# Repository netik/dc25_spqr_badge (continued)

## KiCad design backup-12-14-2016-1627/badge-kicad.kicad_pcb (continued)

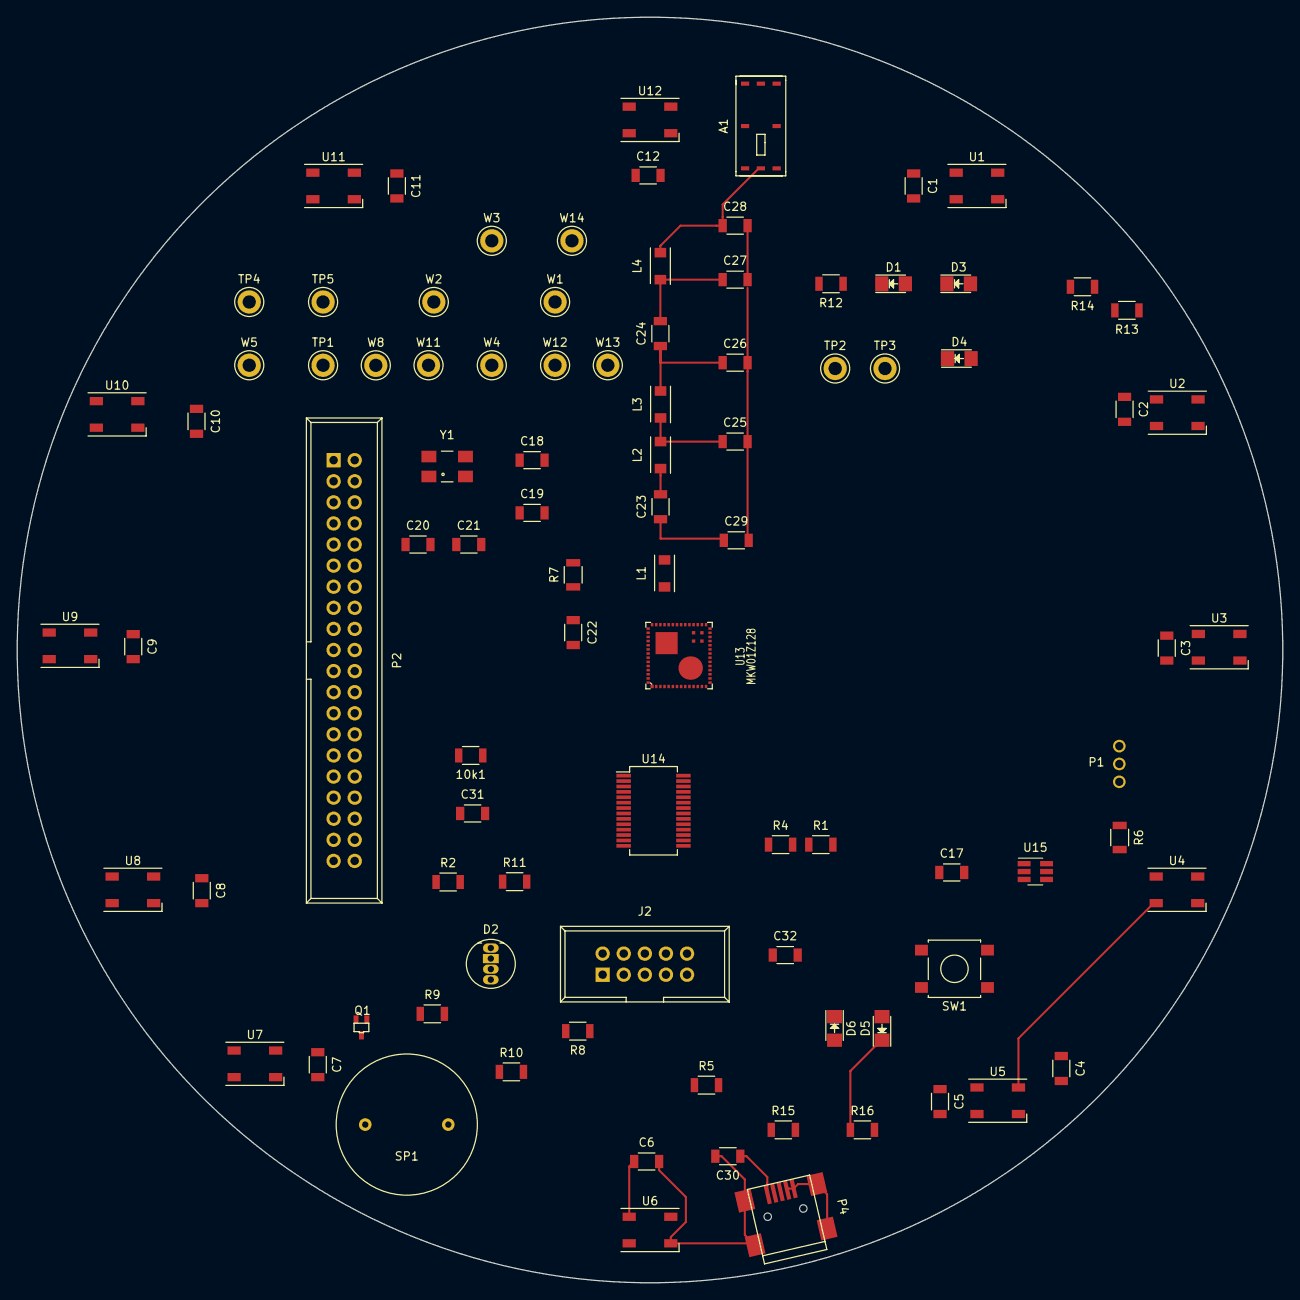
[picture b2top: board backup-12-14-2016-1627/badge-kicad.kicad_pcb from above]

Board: 4 copper layers, 152.4 x 152.4 mm, 94 parts (1 on the bottom side), 72 nets.

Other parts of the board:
10k1: R; R_1206

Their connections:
unnamed 11: 10k1.1; also elsewhere on the board
VUSB: 10k1.2; also elsewhere on the board

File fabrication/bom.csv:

reference_designator,qty,mpn,value,description,partcost,laborcost
A1,1,7488910092,7488910092_ANTENNA,SMD Aerial [Würth Elektronik] 7488910092 SMD Aerial,4.884,0.555
BT1,1,1769,Battery 3.7v 1000mAh,JST-PH 2-Pin SMT Right Angle Connector,0.990,0.270
C1,1,MF-CAP-0805-0.1uF,100nF,Capacitor MLCC 0805 0.1uF -20% +80% 50V,0.169,0.000
C10,1,MF-CAP-0805-0.1uF,100nF,Capacitor MLCC 0805 0.1uF -20% +80% 50V,0.169,0.000
C11,1,MF-CAP-0805-0.1uF,100nF,Capacitor MLCC 0805 0.1uF -20% +80% 50V,0.169,0.000
C12,1,MF-CAP-0805-0.1uF,100nF,Capacitor MLCC 0805 0.1uF -20% +80% 50V,0.169,0.000
C13,1,MF-CAP-0805-1uF,1uF,"Capacitor MLCC 0805 1uF -20%, +80% 16V",0.066,0.000
C14,1,CL21A106KQFNNNG,10uF,CL21 Series 10 uF 6.3V ±10 % Tolerance X5R SMT Multilayer Ceramic Capacitor,0.396,1.665
C15,1,CL21A106KQFNNNG,10uF,CL21 Series 10 uF 6.3V ±10 % Tolerance X5R SMT Multilayer Ceramic Capacitor,0.396,1.665
C17,1,GRM21BR60G107ME15L,100uF,0805 100 uF 4 V ±20% Tolerance X5R Multilayer Ceramic Chip Capacitor,1.558,0.270
C2,1,MF-CAP-0805-0.1uF,100nF,Capacitor MLCC 0805 0.1uF -20% +80% 50V,0.169,0.000
C20,1,MF-CAP-0805-0.1uF,100nF,Capacitor MLCC 0805 0.1uF -20% +80% 50V,0.169,0.000
C21,1,MF-CAP-0805-0.1uF,100nF,Capacitor MLCC 0805 0.1uF -20% +80% 50V,0.169,0.000
C22,1,MF-CAP-0805-0.1uF,0.1uF,Capacitor MLCC 0805 0.1uF -20% +80% 50V,0.165,0.000
C23,1,08051A6R8CAT2A,6.8pF,Capacitor; Ceramic; Cap 6.8 pF; Tol 0.25 pF; Vol-Rtg 100 VDC; SMT; 0805; C0G(NPO); TR,0.224,0.270
C24,1,CC0805JRNPO9BN101,100pF,0805 100 pF 50 V ±5 % Tolerance NPO Surface Mount Ceramic Capacitor,0.132,0.270
C25,1,251R15S7R5CV4E,7.5pF,Cap Cer 7.5pf 250v Np0 0805,0.264,0.270
C26,1,08051A5R6CAT2A,5.6pF,0805 5.6 pF 100 V ±0.25 pF Tol. C0G/NP0 SMT Multilayer Ceramic Capacitor,0.356,0.270
C27,1,CL21C1R2BBANNNC,1.2pF,Cap Ceramic 1.2pF 50V C0G 0.1pF SMD 0805 125°C Cardboard T/R,0.264,0.540
C28,1,CL21C1R2BBANNNC,1.2pF,Cap Ceramic 1.2pF 50V C0G 0.1pF SMD 0805 125°C Cardboard T/R,0.264,0.540
C29,1,C0805C209C5GACTU,2.0pF,Cap Ceramic 2pF 50V C0G 0.25pF SMD 0805 125C Paper T/R,0.436,0.270
C3,1,MF-CAP-0805-0.1uF,100nF,Capacitor MLCC 0805 0.1uF -20% +80% 50V,0.169,0.000
C30,1,MF-CAP-0805-0.1uF,0.1uF,Capacitor MLCC 0805 0.1uF -20% +80% 50V,0.165,0.000
C31,1,CL21A106KQFNNNG,10uF,CL21 Series 10 uF 6.3V ±10 % Tolerance X5R SMT Multilayer Ceramic Capacitor,0.396,1.665
C32,1,MF-CAP-0805-0.1uF,0.1uF,Capacitor MLCC 0805 0.1uF -20% +80% 50V,0.165,0.000
C4,1,MF-CAP-0805-0.1uF,100nF,Capacitor MLCC 0805 0.1uF -20% +80% 50V,0.169,0.000
C5,1,MF-CAP-0805-0.1uF,100nF,Capacitor MLCC 0805 0.1uF -20% +80% 50V,0.169,0.000
C6,1,MF-CAP-0805-0.1uF,100nF,Capacitor MLCC 0805 0.1uF -20% +80% 50V,0.169,0.000
C7,1,MF-CAP-0805-0.1uF,100nF,Capacitor MLCC 0805 0.1uF -20% +80% 50V,0.169,0.000
C8,1,MF-CAP-0805-0.1uF,100nF,Capacitor MLCC 0805 0.1uF -20% +80% 50V,0.169,0.000
C9,1,MF-CAP-0805-0.1uF,100nF,Capacitor MLCC 0805 0.1uF -20% +80% 50V,0.169,0.000
D1,1,MF-LED-0805-RED,RED PWROK,Red LED 638nm 25mcd 0805,0.088,0.000
D2,1,150080BS75000,BLUE SDIO,"LED, 0805, BLUE, 145MCD, 470NM; Bulb Size: -; LED Colour: Bleu; Luminous Intensity",0.238,0.555
D3,1,MF-LED-0805-RED,RED UTX,Red LED 638nm 25mcd 0805,0.088,0.000
D4,1,MF-LED-0805-GREEN,GREEN URX,Green LED 569nm 12mcd 0805,0.088,0.000
D5,1,MF-LED-0805-RED,RED (CHARGING),Red LED 638nm 25mcd 0805,0.088,0.000
D6,1,MF-LED-0805-GREEN,GRN (DONE),Green LED 569nm 12mcd 0805,0.088,0.000
D7,1,MF-LED-0805-RED,RED RFTX,Red LED 638nm 25mcd 0805,0.088,0.000
D8,1,MF-LED-0805-GREEN,GRN RFRX,Green LED 569nm 12mcd 0805,0.088,0.000
J2,1,M50-3500542,JTAG,"Header, Straight, 2row, 10way",1.558,3.330
L1,1,KL732ATTE4N7C,0.0047 uH,Inductor RF Chip Thin Film Multilayer 4.7nH 0.2nH 500MHz 25Q-Factor 700mA 500mOhm DCR 0805 Automotive T/R,0.845,0.270
L2,1,IMC0805ER6N8J01,0.0068 uH,Ind High Frequency Wirewound 6.8nH 5% 250MHz 60Q-Factor Ceramic 600mA 0805 T/R,0.343,0.540
L3,1,IMC0805ER6N8J01,0.0068 uH,Ind High Frequency Wirewound 6.8nH 5% 250MHz 60Q-Factor Ceramic 600mA 0805 T/R,0.343,0.540
L4,1,36502A15NJTDG,15 NH,"Surface Mount High Frequency Inductor, 36502A Series, 15 nH, 5%, 0805 [2012 Metric], 3.4 GHz",0.211,0.270
P1,1,TM1000Q,TM1000,"SENSOR, TILT, 45DEG, 24V; Beam Angle: 45°; Switching Voltage: 24V; Output Current: 20mA; Sensor Body Material: -",2.033,0.555
P2,1,1-215307-0,CONN_02X20,Socket; pin strips; HV-100; female; PIN: 20; straight; 2,3.406,3.330
P4,1,105017-0001,USB_OTG,Conn USB Type B RCP 5 POS 0.65mm Solder RA Thru-Hole 5 Terminal 1 Port Embossed T/R,0.964,0.675
PARTS$0.000,1,,FTDI BACKUP,MPN to consign or search,0.000,0.000
Q1,1,MMBT3904LT1G,MNBT3904,MMBT Series 40 V 200 mA SMT NPN Silicon General Purpose Transistor - SOT-23,0.132,0.405
R1,1,MF-RES-0805-1K,1K,Resistor Thick Film 0805 1K Ohm 5% 125mW 150V,0.055,0.000
R10,1,MF-RES-0805-220,220,Resistor Thick Film 0805 220 Ohm 5% 125mW 150V,0.220,0.000
R11,1,MF-RES-0805-220,220,Resistor Thick Film 0805 220 Ohm 5% 125mW 150V,0.220,0.000
R12,1,MF-RES-0805-220,220,Resistor Thick Film 0805 220 Ohm 5% 125mW 150V,0.220,0.000
R13,1,MF-RES-0805-1K,1k,Resistor Thick Film 0805 1K Ohm 5% 125mW 150V,0.220,0.000
R14,1,MF-RES-0805-1K,1k,Resistor Thick Film 0805 1K Ohm 5% 125mW 150V,0.220,0.000
R15,1,MF-RES-0805-1K,1k,Resistor Thick Film 0805 1K Ohm 5% 125mW 150V,0.220,0.000
R16,1,MF-RES-0805-1K,1k,Resistor Thick Film 0805 1K Ohm 5% 125mW 150V,0.220,0.000
R2,1,MF-RES-0805-100,100,Resistor Thick Film 0805 100 Ohm 5% 125mW 150V,0.110,0.000
R3,1,MF-RES-0805-10K,10k,Resistor Thick Film 0805 10K Ohm 5% 125mW 150V,0.110,0.000
R4,1,MF-RES-0805-100,120,Resistor Thick Film 0805 100 Ohm 5% 125mW 150V,0.055,0.000
R5,1,MF-RES-0805-2K,2k,Resistor Thick Film 0805 2K Ohm5% 125W 150V,0.055,0.000
R6,1,MF-RES-0805-10K,10k,Resistor Thick Film 0805 10K Ohm 5% 125mW 150V,0.110,0.000
R7,1,MF-RES-0805-100,100,Resistor Thick Film 0805 100 Ohm 5% 125mW 150V,0.110,0.000
R8,1,MF-RES-0805-10K,10K,Resistor Thick Film 0805 10K Ohm 5% 125mW 150V,0.055,0.000
R9,1,MF-RES-0805-220,220,Resistor Thick Film 0805 220 Ohm 5% 125mW 150V,0.220,0.000
SP1,1,PS1720P02,TDK PS1720P02,PS Series Ø17 mm 8 x 10 mm 70 dB 3 V 2 KHz Piezoelectronic Buzzer,0.964,0.555
SW1,1,TL3301NF160QG,SW_PUSH,TL3301 Series SPST 1.6 N Round Button Gull Wing Surface Mount Tactile Switch,0.515,0.555
U1,1,WS2812B,WS2812B,Integrated Control Driver RGB LED 5050,2.640,5.178
U10,1,WS2812B,WS2812B,Integrated Control Driver RGB LED 5050,2.640,5.178
U11,1,WS2812B,WS2812B,Integrated Control Driver RGB LED 5050,2.640,5.178
U12,1,WS2812B,WS2812B,Integrated Control Driver RGB LED 5050,2.640,5.178
U13,1,MKW01Z128CHN,MKW01Z128,"Kinetis KW01: sub 1GHz Wireless Radio MCU, 48MHz Cortex-M0+, 128KB Flash, 16KB SRAM, 60-LGA",5.306,3.330
U14,1,FT232RL-TUBE,FT232RL SSOP,USB-to-UART 1-CH 256byte FIFO 5V 28-Pin SSOP Tube,5.940,3.330
U15,1,TPS76333DBVR,TPS76333,"Low Iq, 150-mA, Low-Dropout Linear Regulators 5-SOT-23 -40 to 125",1.175,0.675
U16,1,MCP73831T-2ACI/OT,MCP73831T-2ACI/OT,"supervisor, pin, supply, battery, number, single, voltage, ic, Power Management, current, management, temperature, mi...",0.766,0.675
U2,1,WS2812B,WS2812B,Integrated Control Driver RGB LED 5050,2.640,5.178
U3,1,WS2812B,WS2812B,Integrated Control Driver RGB LED 5050,2.640,5.178
U4,1,WS2812B,WS2812B,Integrated Control Driver RGB LED 5050,2.640,5.178
U5,1,WS2812B,WS2812B,Integrated Control Driver RGB LED 5050,2.640,5.178
U6,1,WS2812B,WS2812B,Integrated Control Driver RGB LED 5050,2.640,5.178
U7,1,WS2812B,WS2812B,Integrated Control Driver RGB LED 5050,2.640,5.178
U8,1,WS2812B,WS2812B,Integrated Control Driver RGB LED 5050,2.640,5.178
U9,1,WS2812B,WS2812B,Integrated Control Driver RGB LED 5050,2.640,5.178
Y1,1,AWSCR-32.00CW-T,AWSCR-XTAL,Built-In Capacitance Ceramic Resonator,0.607,1.185

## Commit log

2016-12-22 remove backups now that we use git, add bom scrape tools
2016-12-23 replace parts with MF parts to save money, add power switch
2016-12-28 rebuild RF section to match KW01 dev board
2017-01-17 add backup of files as sent to macrofab for rev1
2017-01-17 rename backup folders
2017-01-17 checkpoint v2 board
2017-01-17 checkpoint v2 board backup files
2017-02-06 new board shape, now with DAC, audio amp, and joypad
2017-02-07 add silkscreens and fix some traces
2017-02-07 add badge audio
2017-02-07 Fix the reset button which was tied to ground by mistake
2017-02-07 swap PTD7 and PTB1
2017-02-07 add text and logos to pcb
2017-02-07 Final rev2, clean up rev1
2017-02-08 add laurel designs back, switch some caps to 0603 based on BOM
2017-02-08 Revision 2 final layout.
    Add connection for missing VBAT connector, add some decoupling caps on KW01
    Output drill files again.
2017-02-08 fix typo
2017-02-08 redo the drill files, send it to macrofab!
2017-02-09 update xyrs bom, fix typo
2017-02-09 Move the P4-Net trace far, far away from H4. Potential issue if we resize the hole
2017-03-24 update for fabrication rev3
2017-04-19 check in changes before modifiying footprint for rev4
2017-04-20 update footprints, check in everything before rev4
2017-05-04 update for rev4
2017-05-04 add missing files
2017-05-04 add rev4
2017-05-04 cleanup
2017-05-23 final commit for production
2017-05-26 minor cleanups
2017-06-15 push last changes
2017-06-15 Create README.md
    Update readme with standoffs, screens, and other non-BOM parts
2017-07-10 Make some minot tweaks to work with release versions of KiCad
    John used a nightly build of KiCad to generate the PCB for this project.
    The nightly builds have some features not found in the release versions,
    including some changes to the PCB file format. The main difference is the
    use of the diff_pair_gap and diff_pair_width keywords, which released
    versions of KiCad do not understand.
    Fortunately, becuase all KiCad files are text, we can work around this by
